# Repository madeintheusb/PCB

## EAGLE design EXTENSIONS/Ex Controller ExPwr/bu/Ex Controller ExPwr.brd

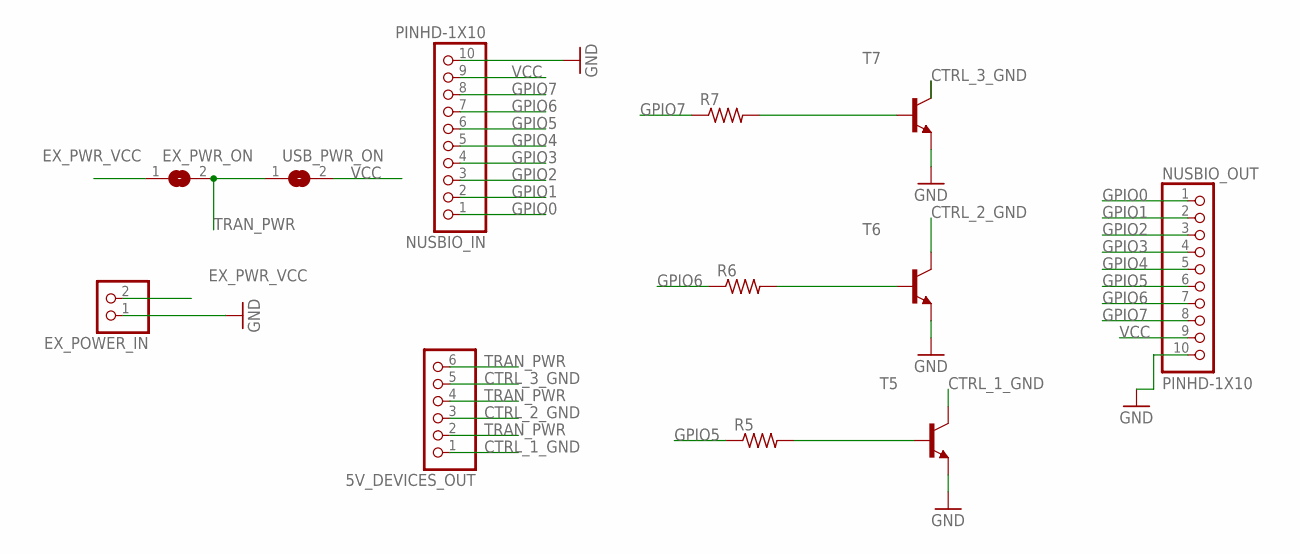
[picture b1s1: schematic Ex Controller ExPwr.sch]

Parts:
5V_DEVICES_OUT: PINHD-1X6; 1X06
EX_POWER_IN: PINHD-1X2; 1X02
EX_PWR_ON: SOLDERJUMPERREFLOW; SOLDERJUMPER_REFLOW
NUSBIO_IN: PINHD-1X10; 1X10-BIG
NUSBIO_OUT: PINHD-1X10; 1X10-BIG
R5, R6, R7: R-US_R0805; R0805
T5, T6, T7: MMBT3904LT1-NPN-SOT23-BEC; SOT23-BEC
USB_PWR_ON: SOLDERJUMPERREFLOW; SOLDERJUMPER_REFLOW

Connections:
CTRL_1_GND: 5V_DEVICES_OUT.1, T5.C
CTRL_2_GND: 5V_DEVICES_OUT.3, T6.C
CTRL_3_GND: 5V_DEVICES_OUT.5, T7.C
EX_PWR_VCC: EX_POWER_IN.2, EX_PWR_ON.1
GND: EX_POWER_IN.1, NUSBIO_IN.10, NUSBIO_OUT.10, T5.E, T6.E, T7.E
GPIO0: NUSBIO_IN.1, NUSBIO_OUT.1
GPIO1: NUSBIO_IN.2, NUSBIO_OUT.2
GPIO2: NUSBIO_IN.3, NUSBIO_OUT.3
GPIO3: NUSBIO_IN.4, NUSBIO_OUT.4
GPIO4: NUSBIO_IN.5, NUSBIO_OUT.5
GPIO5: NUSBIO_IN.6, NUSBIO_OUT.6, R5.1
GPIO6: NUSBIO_IN.7, NUSBIO_OUT.7, R6.1
GPIO7: NUSBIO_IN.8, NUSBIO_OUT.8, R7.1
unnamed: R7.2, T7.B
unnamed: R5.2, T5.B
unnamed: R6.2, T6.B
TRAN_PWR: 5V_DEVICES_OUT.2, 5V_DEVICES_OUT.4, 5V_DEVICES_OUT.6, EX_PWR_ON.2, USB_PWR_ON.1
VCC: NUSBIO_IN.9, NUSBIO_OUT.9, USB_PWR_ON.2

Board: 2 copper layers, 12 parts (0 on the bottom side), 18 nets, no tracks yet.

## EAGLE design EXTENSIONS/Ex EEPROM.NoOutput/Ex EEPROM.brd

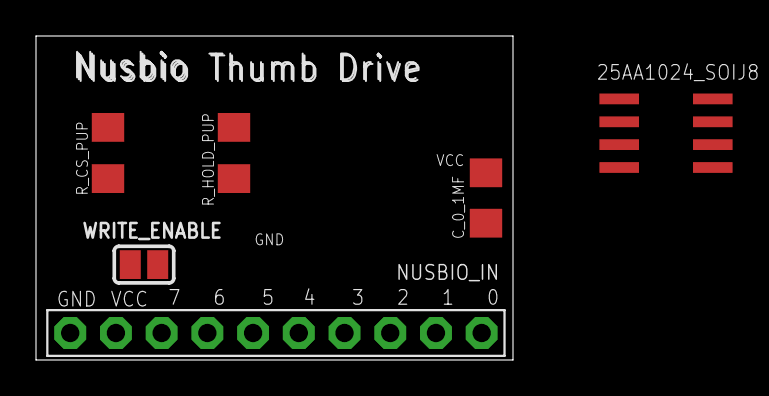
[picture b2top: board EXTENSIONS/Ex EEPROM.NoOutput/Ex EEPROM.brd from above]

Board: 2 copper layers, 26.5 x 18.0 mm, 6 parts (0 on the bottom side), 8 nets, no tracks yet.

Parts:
25AA1024_SOIJ8: 25AA080SN; SO-08
C_0_1MF: C1206
NUSBIO_IN: PINHD-1X10; 1X10-BIG
R_CS_PUP: R1206
R_HOLD_PUP: R1206
WRITE_ENABLE: SOLDERJUMPER_REFLOW

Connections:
CS: 25AA1024_SOIJ8.1, NUSBIO_IN.4, R_CS_PUP.2
GND: 25AA1024_SOIJ8.4, C_0_1MF.2, NUSBIO_IN.10
HOLD: 25AA1024_SOIJ8.7, R_HOLD_PUP.2
MISO: 25AA1024_SOIJ8.2, NUSBIO_IN.3
MOSI: 25AA1024_SOIJ8.5, NUSBIO_IN.2
unnamed: 25AA1024_SOIJ8.3, WRITE_ENABLE.2
SCK: 25AA1024_SOIJ8.6, NUSBIO_IN.1
VCC: 25AA1024_SOIJ8.8, C_0_1MF.1, NUSBIO_IN.9, R_CS_PUP.1, R_HOLD_PUP.1, WRITE_ENABLE.1

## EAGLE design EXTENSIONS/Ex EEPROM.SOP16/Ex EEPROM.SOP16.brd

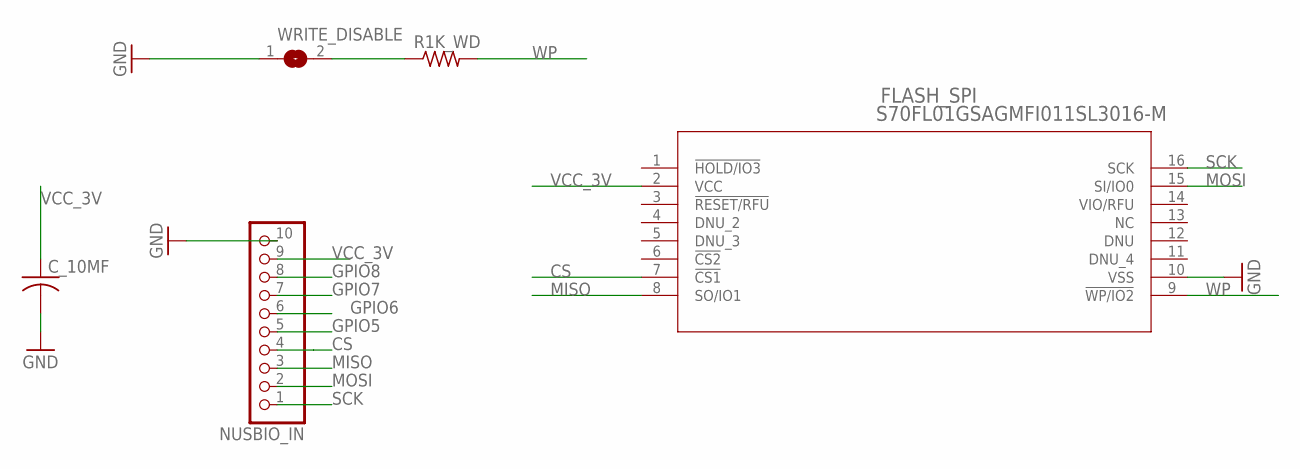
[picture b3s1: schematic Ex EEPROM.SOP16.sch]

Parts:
C_10MF: C-USC1206; C1206
FLASH_SPI: S70FL01GSAGMFI011SL3016-M; SL3016-M
NUSBIO_IN: PINHD-1X10; 1X10-BIG
R1K_WD: R-US_R1206; R1206
WRITE_DISABLE: SOLDERJUMPERREFLOW; SOLDERJUMPER_REFLOW

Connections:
CS: FLASH_SPI.7 (!CS1), NUSBIO_IN.4
GND: C_10MF.2, FLASH_SPI.10 (VSS), NUSBIO_IN.10, WRITE_DISABLE.1
GPIO5: NUSBIO_IN.5
GPIO6: NUSBIO_IN.6
GPIO7: NUSBIO_IN.7
GPIO8: NUSBIO_IN.8
MISO: FLASH_SPI.8 (SO/IO1), NUSBIO_IN.3
MOSI: FLASH_SPI.15 (SI/IO0), NUSBIO_IN.2
unnamed: R1K_WD.1, WRITE_DISABLE.2
SCK: FLASH_SPI.16 (SCK), NUSBIO_IN.1
VCC_3V: C_10MF.1, FLASH_SPI.2 (VCC), NUSBIO_IN.9
WP: FLASH_SPI.9 (!WP/IO2), R1K_WD.2

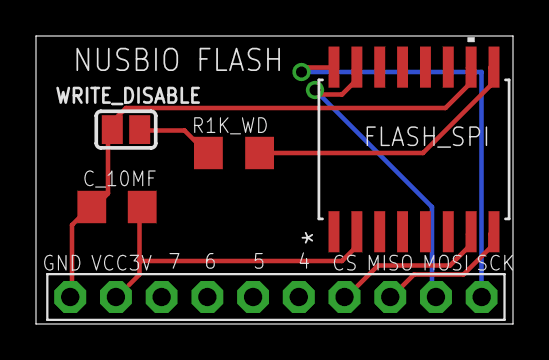
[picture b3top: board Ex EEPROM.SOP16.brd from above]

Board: 2 copper layers, 26.5 x 16.0 mm, 5 parts (0 on the bottom side), 8 nets.

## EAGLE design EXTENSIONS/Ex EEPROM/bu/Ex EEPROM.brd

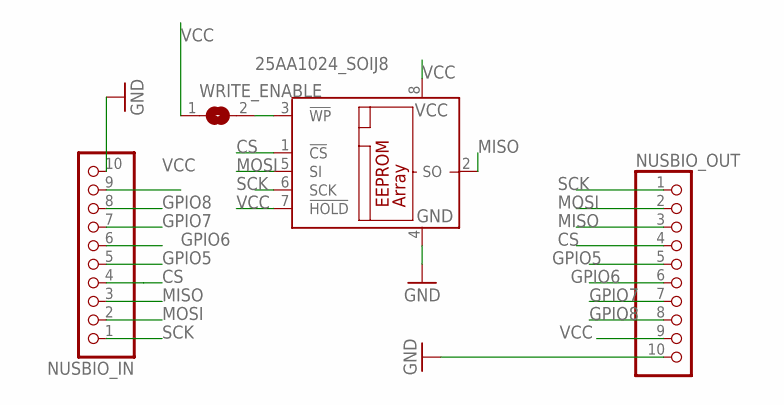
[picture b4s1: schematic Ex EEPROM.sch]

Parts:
25AA1024_SOIJ8: 25AA080SN; SO-08
NUSBIO_IN: PINHD-1X10; 1X10-BIG
NUSBIO_OUT: PINHD-1X10; 1X10-BIG
WRITE_ENABLE: SOLDERJUMPERREFLOW; SOLDERJUMPER_REFLOW

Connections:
CS: 25AA1024_SOIJ8.1 (!CS), NUSBIO_IN.4, NUSBIO_OUT.4
GND: 25AA1024_SOIJ8.4 (GND), NUSBIO_IN.10, NUSBIO_OUT.10
GPIO5: NUSBIO_IN.5, NUSBIO_OUT.5
GPIO6: NUSBIO_IN.6, NUSBIO_OUT.6
GPIO7: NUSBIO_IN.7, NUSBIO_OUT.7
GPIO8: NUSBIO_IN.8, NUSBIO_OUT.8
MISO: 25AA1024_SOIJ8.2 (SO), NUSBIO_IN.3, NUSBIO_OUT.3
MOSI: 25AA1024_SOIJ8.5 (SI), NUSBIO_IN.2, NUSBIO_OUT.2
unnamed: 25AA1024_SOIJ8.3 (!WP), WRITE_ENABLE.2
SCK: 25AA1024_SOIJ8.6 (SCK), NUSBIO_IN.1, NUSBIO_OUT.1
VCC: 25AA1024_SOIJ8.7 (!HOLD), 25AA1024_SOIJ8.8 (VCC), NUSBIO_IN.9, NUSBIO_OUT.9, WRITE_ENABLE.1

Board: 2 copper layers, 4 parts (0 on the bottom side), 11 nets, no tracks yet.

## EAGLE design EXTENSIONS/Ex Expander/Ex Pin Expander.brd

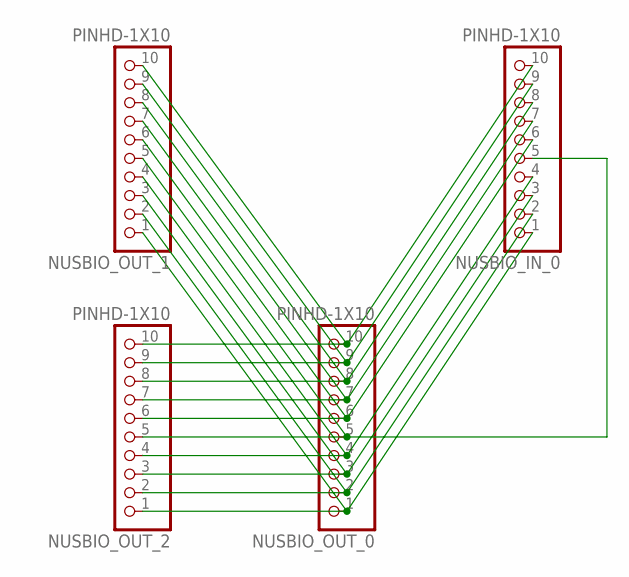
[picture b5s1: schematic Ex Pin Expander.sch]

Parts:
NUSBIO_IN_0: PINHD-1X10; 1X10-BIG
NUSBIO_OUT_0, NUSBIO_OUT_1, NUSBIO_OUT_2: PINHD-1X10; 1X10-BIG

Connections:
unnamed: NUSBIO_IN_0.10, NUSBIO_OUT_0.10, NUSBIO_OUT_1.10, NUSBIO_OUT_2.10
unnamed: NUSBIO_IN_0.9, NUSBIO_OUT_0.9, NUSBIO_OUT_1.9, NUSBIO_OUT_2.9
unnamed: NUSBIO_IN_0.8, NUSBIO_OUT_0.8, NUSBIO_OUT_1.8, NUSBIO_OUT_2.8
unnamed: NUSBIO_IN_0.7, NUSBIO_OUT_0.7, NUSBIO_OUT_1.7, NUSBIO_OUT_2.7
unnamed: NUSBIO_IN_0.6, NUSBIO_OUT_0.6, NUSBIO_OUT_1.6, NUSBIO_OUT_2.6
unnamed: NUSBIO_IN_0.5, NUSBIO_OUT_0.5, NUSBIO_OUT_1.5, NUSBIO_OUT_2.5
unnamed: NUSBIO_IN_0.4, NUSBIO_OUT_0.4, NUSBIO_OUT_1.4, NUSBIO_OUT_2.4
unnamed: NUSBIO_IN_0.3, NUSBIO_OUT_0.3, NUSBIO_OUT_1.3, NUSBIO_OUT_2.3
unnamed: NUSBIO_IN_0.2, NUSBIO_OUT_0.2, NUSBIO_OUT_1.2, NUSBIO_OUT_2.2
unnamed: NUSBIO_IN_0.1, NUSBIO_OUT_0.1, NUSBIO_OUT_1.1, NUSBIO_OUT_2.1

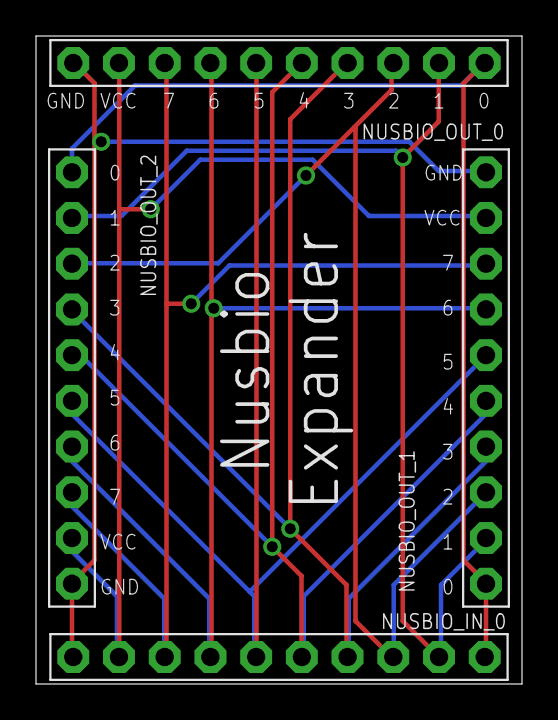
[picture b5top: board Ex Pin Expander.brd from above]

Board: 2 copper layers, 27.0 x 36.0 mm, 4 parts (0 on the bottom side), 10 nets.

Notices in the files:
parts and their libraries:
microbuilder: This work is placed in the public domain, and may be freely used for commercial and non-commercial work with the following conditions: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
